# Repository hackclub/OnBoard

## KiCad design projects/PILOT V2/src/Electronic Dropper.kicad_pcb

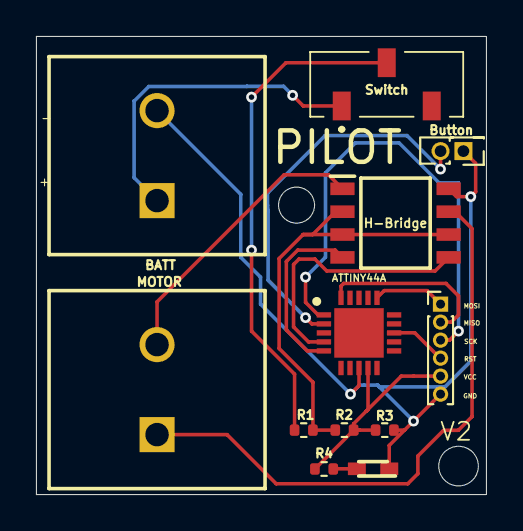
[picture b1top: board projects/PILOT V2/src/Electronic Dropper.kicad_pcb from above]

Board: 2 copper layers, 25.0 x 25.4 mm, 12 parts (0 on the bottom side), 15 nets.

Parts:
ATTINY44A: ATTINY44A-MU; ATTiny44a-MU
BATT: Battery; 1800408
H-Bridge: BD6221F-E2; SOIC127P620X171-8N
LED1: LED; Green led
MOTOR: 1800408
Programming-Pins1: Conn_01x06_Socket; PinHeader_1x06_P1.00mm_Vertical
R1: 270; R_0402_1005Metric
R2: 200; R_0402_1005Metric
R3: 1000; R_0402_1005Metric
R4: 300; R_0402_1005Metric
SW1: SW_Push; PinHeader_2x01_P1.27mm_Vertical
Switch: JS102011JCQN

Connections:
FIN: ATTINY44A.5 ((ADC0/AREF/PCINT0)_PA0), H-Bridge.4 (FIN)
GND: ATTINY44A.8 (GND), BATT.2 (-), H-Bridge.8 (GND), LED1.1 (K), Programming-Pins1.6, R3.2, SW1.1
unnamed: ATTINY44A.2 ((ADC3/T0/PCINT3)_PA3), SW1.2
unnamed: ATTINY44A.1 ((ADC4/USCK/SCL/T1/PCINT4)_PA4), Programming-Pins1.3
unnamed: ATTINY44A.20 (PA5_(ADC5/DO/MISO/OC1B/PCINT5)), Programming-Pins1.2
unnamed: ATTINY44A.16 (PA6_(PCINT6/OC1A/SDA/MOSI/DI/ADC6)), Programming-Pins1.1
unnamed: ATTINY44A.13 (PB3_(PCINT11/~RESET/DW)), Programming-Pins1.4
unnamed: BATT.1 (+), Switch.1
unnamed: H-Bridge.1 (OUT1), MOTOR.2
unnamed: H-Bridge.7 (OUT2), MOTOR.1
unnamed: LED1.2 (A), R4.2
unnamed: R1.2, Switch.2
RIN: ATTINY44A.4 ((ADC1/AIN0/PCINT1)_PA1), H-Bridge.5 (RIN)
VCC: ATTINY44A.9 (VCC), Programming-Pins1.5, R2.2, R3.1, R4.1
VCCQ: H-Bridge.2 (VCC_1), H-Bridge.3 (VCC_2), H-Bridge.6 (VREF), R1.1, R2.1

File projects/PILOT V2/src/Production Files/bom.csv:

Designator,Footprint,Quantity,Value,LCSC Part #
ATTINY44A,ATTiny44a-MU,1,ATTINY44A-MU,
BATT,1800408,1,Battery,
LED1,Green led,1,LED,
MOTOR,1800408,1,1800408,
R1,0402,1,270,
R2,0402,1,200,
R3,0402,1,1000,
R4,0402,1,300,
Switch,JS102011JCQN,1,JS102011JCQN,

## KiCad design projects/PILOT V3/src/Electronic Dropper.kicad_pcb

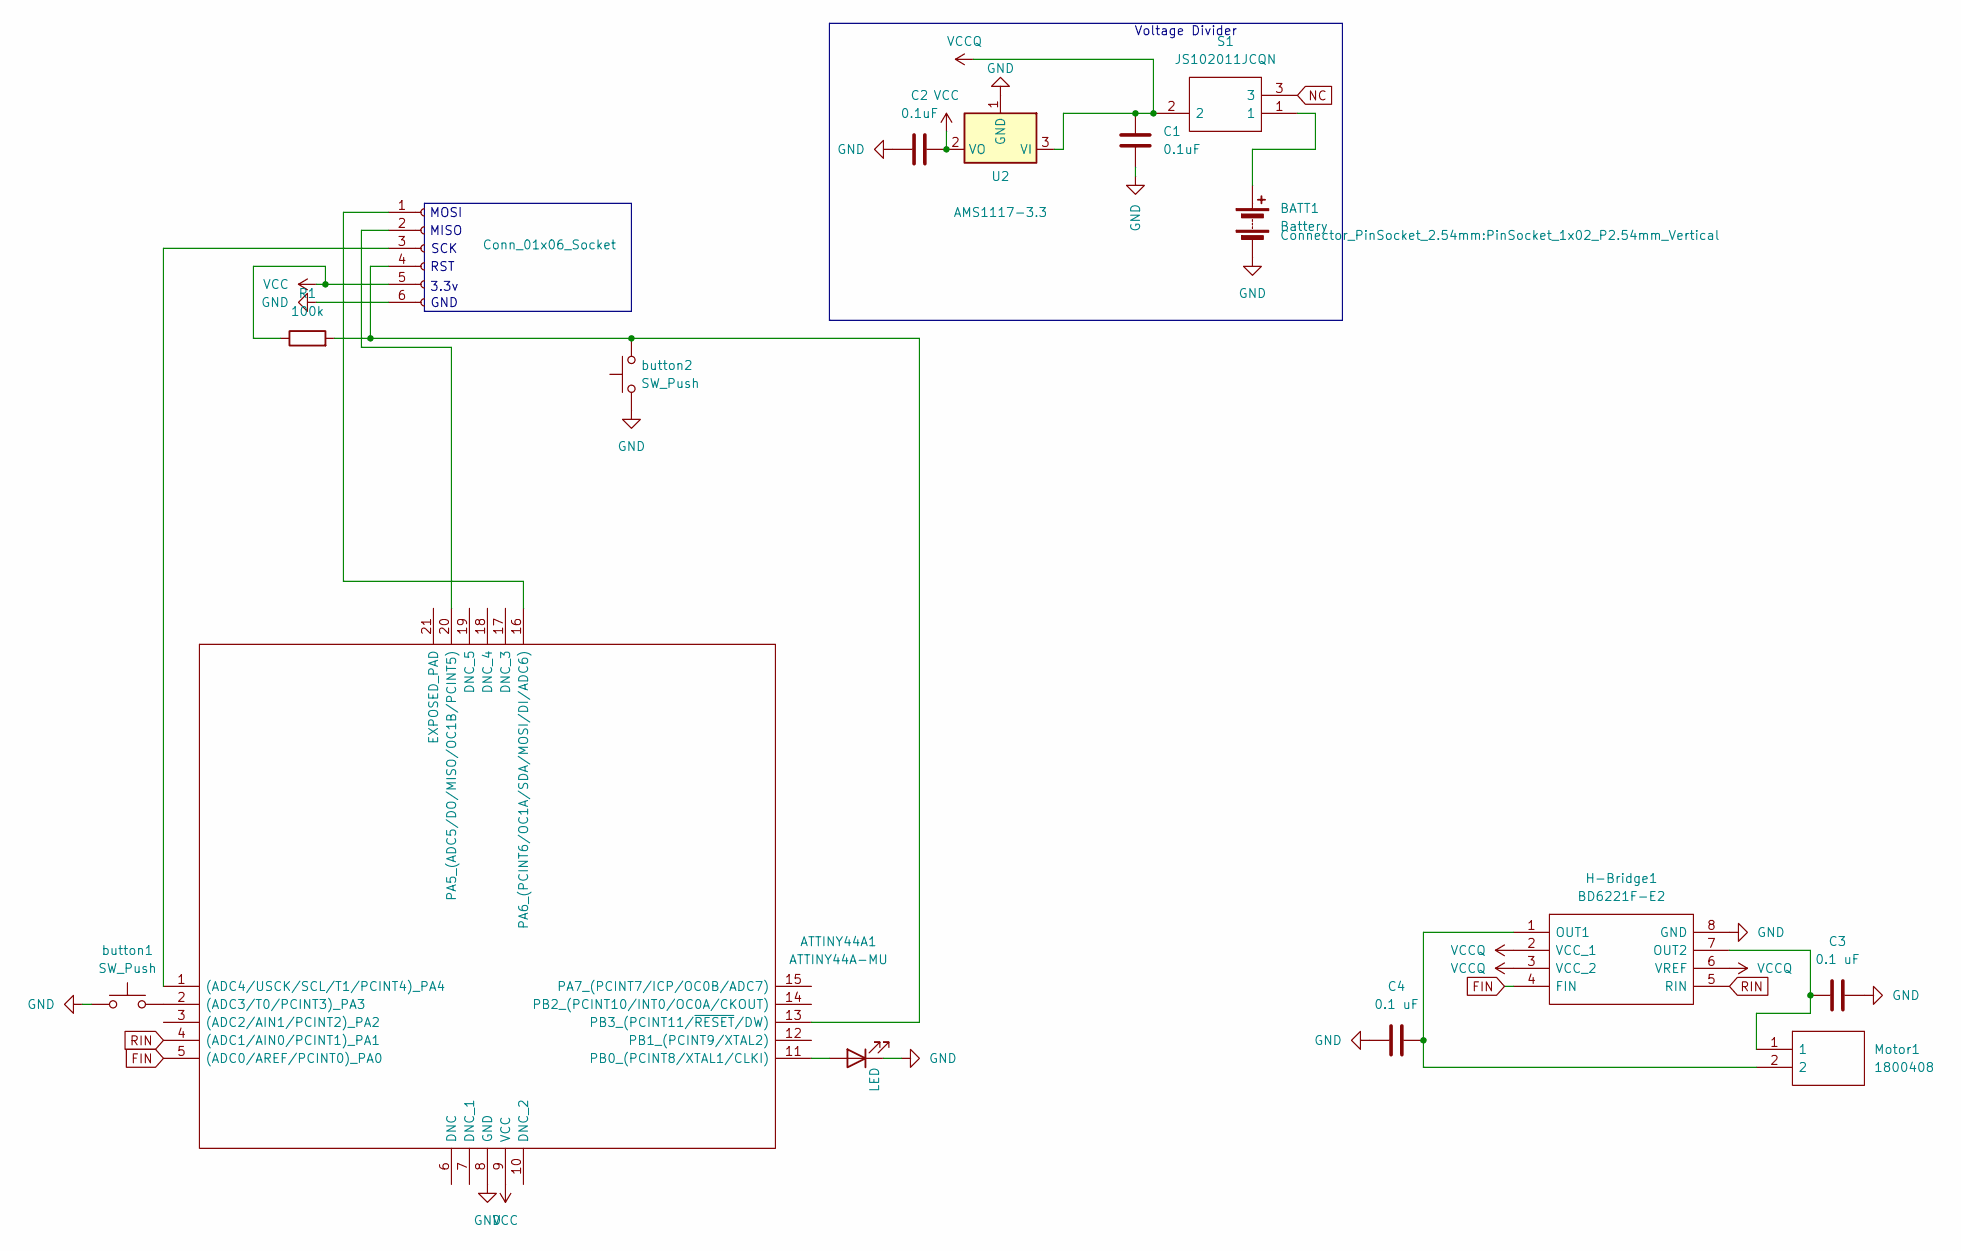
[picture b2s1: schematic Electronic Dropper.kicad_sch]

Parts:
ATTINY44A1: ATTINY44A-MU; ATTiny44a-MU; Manufacturer_Part_Number ATTINY44A-MU; Mouser Part Number 556-ATTINY44A-MU
BATT1: Battery; PinSocket_1x02_P2.54mm_Vertical
C1, C2: 0.1uF; C_0805_2012Metric
C3, C4: 0.1 uF; C_0805_2012Metric
H-Bridge1: BD6221F-E2; SOIC127P620X171-8N; Mouser Part Number 755-BD6221F-E2
LED1: LED; Green led
Motor1: 1800408; PinSocket_1x02_P2.54mm_Vertical
Programming-Pins1: Conn_01x06_Socket; PinHeader_1x06_P2.54mm_Vertical
R1: 100k; C_0402_1005Metric
S1: JS102011JCQN; Mouser Part Number 611-JS102011JCQN
U2: AMS1117-3.3; SOT-223-3_TabPin2
button1: SW_Push; PinSocket_1x02_P2.54mm_Vertical
button2: SW_Push; SW_PUSH_6mm

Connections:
FIN: ATTINY44A1.5 ((ADC0/AREF/PCINT0)_PA0), H-Bridge1.4 (FIN)
GND: ATTINY44A1.8 (GND), BATT1.2 (-), C1.2, C2.1, C3.2, C4.1, H-Bridge1.8 (GND), LED1.1 (K), Programming-Pins1.6, U2.1 (GND), button1.1, button2.1
NC: S1.3
unnamed: ATTINY44A1.2 ((ADC3/T0/PCINT3)_PA3), button1.2
unnamed: ATTINY44A1.1 ((ADC4/USCK/SCL/T1/PCINT4)_PA4), Programming-Pins1.3
unnamed: ATTINY44A1.20 (PA5_(ADC5/DO/MISO/OC1B/PCINT5)), Programming-Pins1.2
unnamed: ATTINY44A1.16 (PA6_(PCINT6/OC1A/SDA/MOSI/DI/ADC6)), Programming-Pins1.1
unnamed: ATTINY44A1.11 (PB0_(PCINT8/XTAL1/CLKI)), LED1.2 (A)
unnamed: ATTINY44A1.13 (PB3_(PCINT11/~RESET/DW)), Programming-Pins1.4, R1.2, button2.2
unnamed: BATT1.1 (+), S1.1
unnamed: C4.2, H-Bridge1.1 (OUT1), Motor1.2
unnamed: C3.1, H-Bridge1.7 (OUT2), Motor1.1
RIN: ATTINY44A1.4 ((ADC1/AIN0/PCINT1)_PA1), H-Bridge1.5 (RIN)
VCC: ATTINY44A1.9 (VCC), C2.2, Programming-Pins1.5, R1.1, U2.2 (VO)
VCCQ: C1.1, H-Bridge1.2 (VCC_1), H-Bridge1.3 (VCC_2), H-Bridge1.6 (VREF), S1.2, U2.3 (VI)

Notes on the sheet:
MOSI
RST
3.3v
Voltage Divider
GND
MISO
SCK

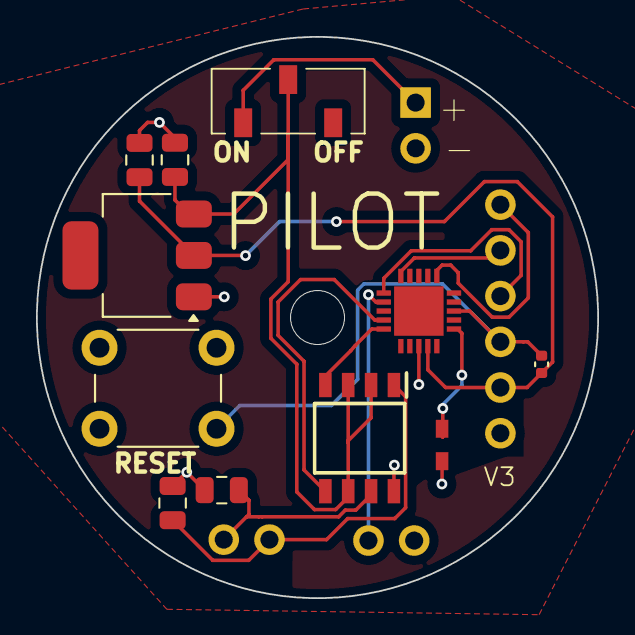
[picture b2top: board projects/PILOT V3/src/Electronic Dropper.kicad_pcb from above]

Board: 2 copper layers, 31.2 x 31.2 mm, 15 parts (0 on the bottom side), 14 nets.

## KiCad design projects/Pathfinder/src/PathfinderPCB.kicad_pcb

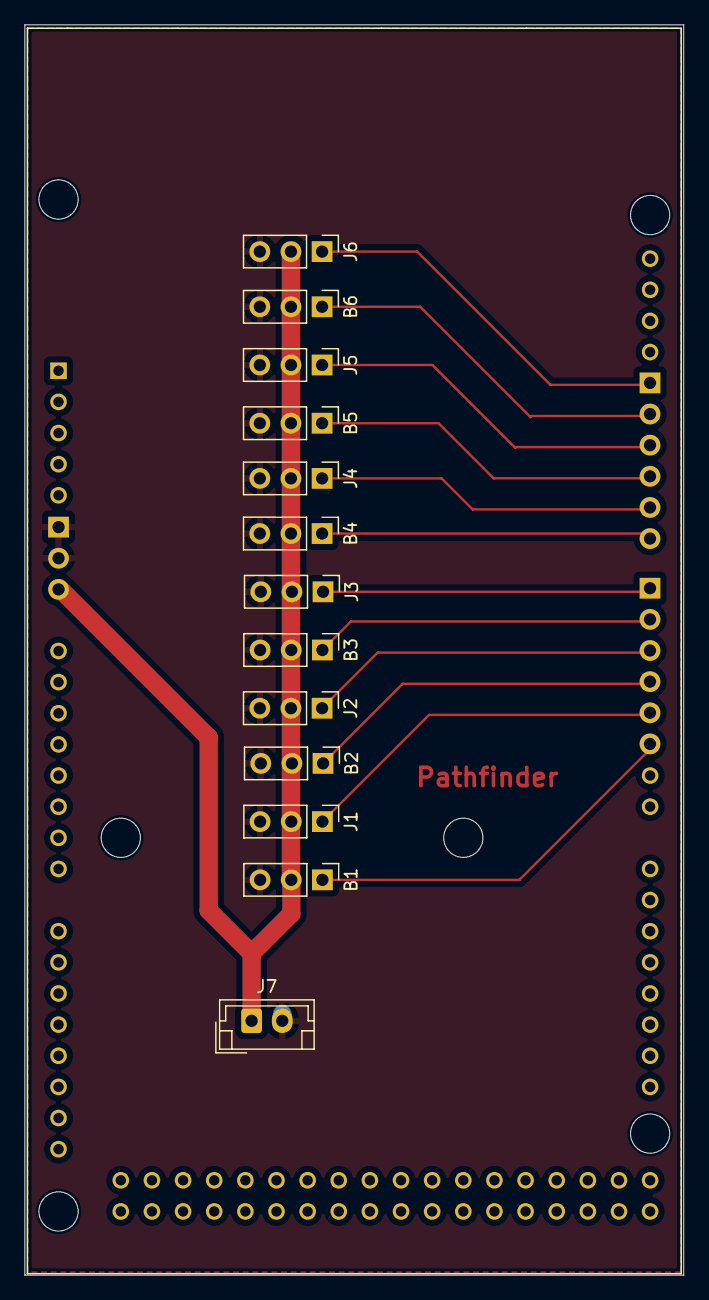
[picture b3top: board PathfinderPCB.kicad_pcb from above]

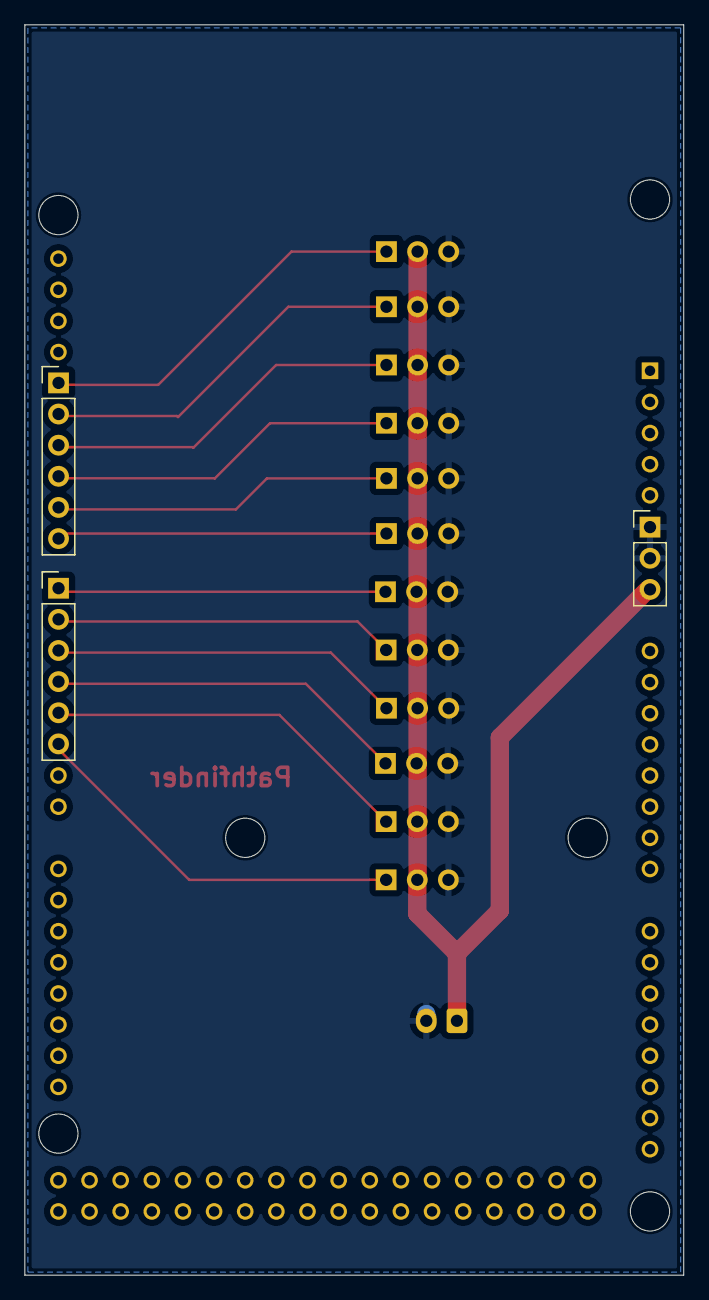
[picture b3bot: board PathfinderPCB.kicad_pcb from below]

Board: 2 copper layers, 53.8 x 102.0 mm, 17 parts (3 on the bottom side), 14 nets.

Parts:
A1: ARDUINO_MEGA_2560_REV3_A000067; ARDUINO_ARDUINO_MEGA_2560_REV3_A000067
B1, B2, B3, B4, B5, B6: Motor_Servo; PinHeader_1x03_P2.54mm_Vertical
J1, J2, J3, J4, J5, J6: Motor_Servo; PinHeader_1x03_P2.54mm_Vertical
J7: Conn_01x02_Pin; JST_EH_B2B-EH-A_1x02_P2.50mm_Vertical
J8, J9: Conn_01x06_Pin; PinHeader_1x06_P2.54mm_Vertical
J10: Conn_01x03_Pin; PinHeader_1x03_P2.54mm_Vertical

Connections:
+5V: B1.2 (5V), B2.2 (5V), B3.2 (5V), B4.2 (5V), B5.2 (5V), B6.2 (5V), J1.2 (5V), J2.2 (5V), J3.2 (5V), J4.2 (5V), J5.2 (5V), J6.2 (5V), J7.1, J10.3
GND: B1.3 (GND), B2.3 (GND), B3.3 (GND), B4.3 (GND), B5.3 (GND), B6.3 (GND), J1.3 (GND), J2.3 (GND), J3.3 (GND), J4.3 (GND), J5.3 (GND), J6.3 (GND), J7.2, J10.1, J10.2
unnamed: B1.1 (PWM), J8.6
unnamed: B2.1 (PWM), J8.4
unnamed: B3.1 (PWM), J8.2
unnamed: B4.1 (PWM), J9.6
unnamed: B5.1 (PWM), J9.4
unnamed: B6.1 (PWM), J9.2
unnamed: J1.1 (PWM), J8.5
unnamed: J2.1 (PWM), J8.3
unnamed: J3.1 (PWM), J8.1
unnamed: J4.1 (PWM), J9.5
unnamed: J5.1 (PWM), J9.3
unnamed: J6.1 (PWM), J9.1

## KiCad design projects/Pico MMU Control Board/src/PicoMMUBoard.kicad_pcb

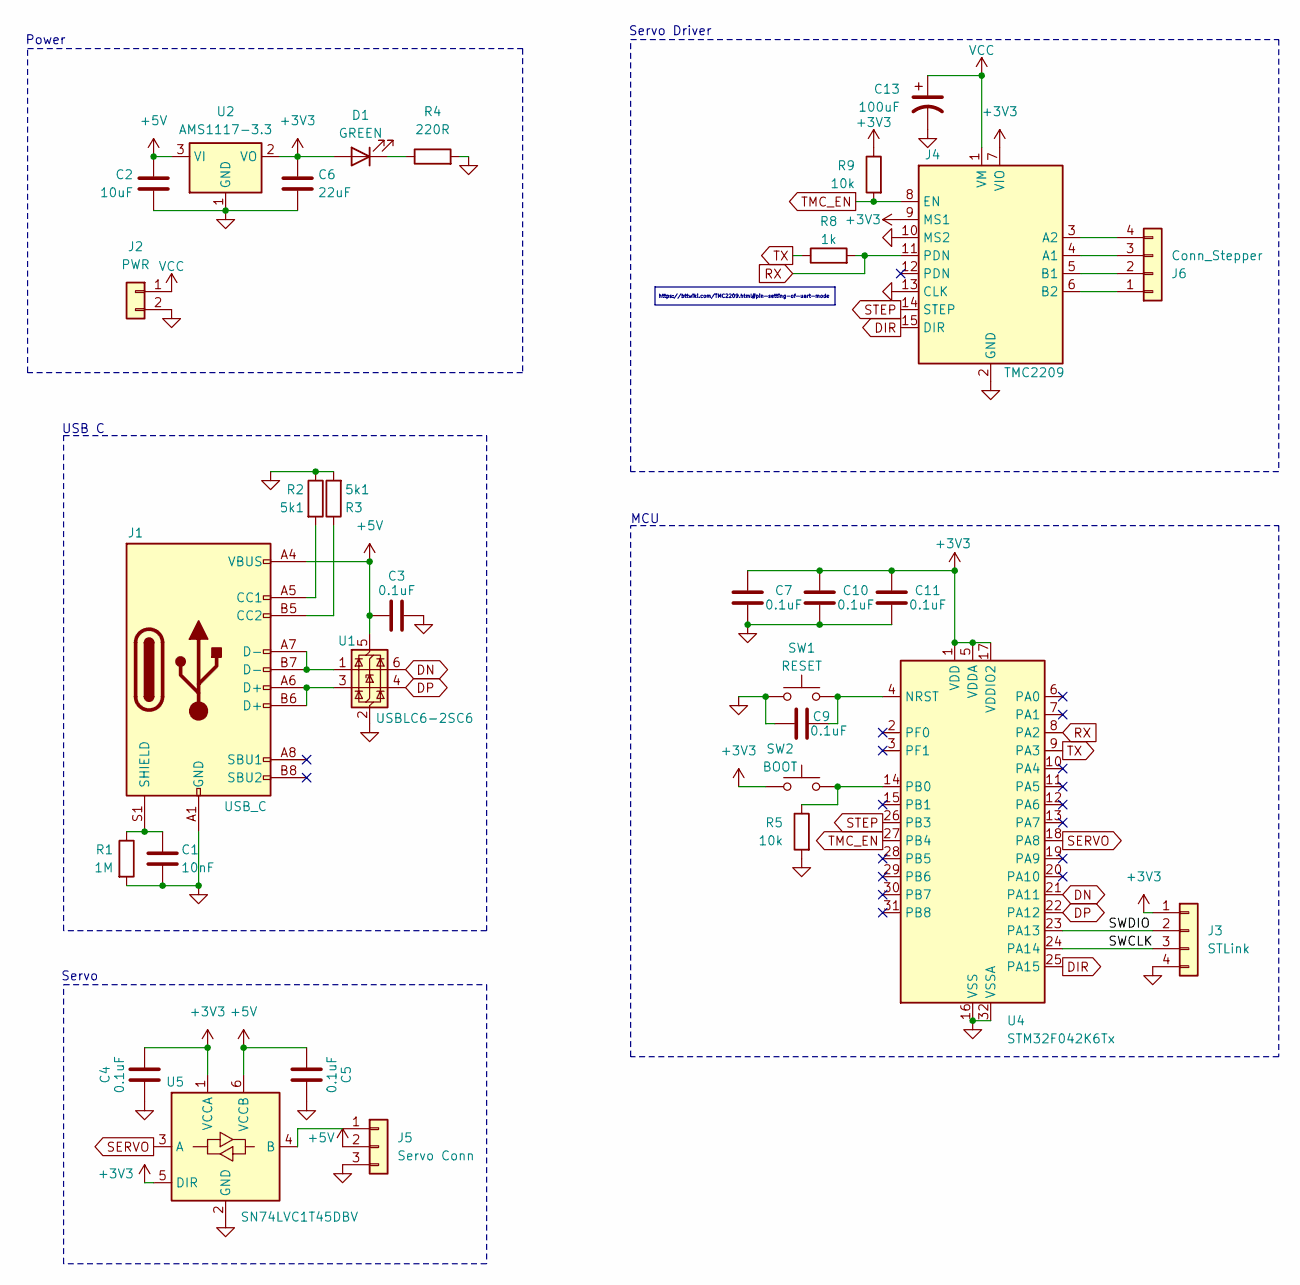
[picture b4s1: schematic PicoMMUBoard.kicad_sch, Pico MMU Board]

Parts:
C1: 10nF; C_0603_1608Metric
C2: 10uF; C_0603_1608Metric
C3, C4, C5, C7, C9, C10, C11: 0.1uF; C_0603_1608Metric
C6: 22uF; C_0603_1608Metric
C13: 100uF; C_Elec_6.3x7.7; LCSC C3151829
D1: GREEN; LED_0805_2012Metric; LCSC C2297
J1: USB_C; USB_C_Receptacle_GCT_USB4105-xx-A_16P_TopMnt_Horizontal; LCSC C165948
J2: PWR; TerminalBlock_MetzConnect_Type073_RT02602HBLU_1x02_P5.08mm_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; LCSC C8465
J3: STLink; PinHeader_1x04_P2.54mm_Vertical
J4: TMC2209
J5: Servo Conn; PinHeader_1x03_P2.54mm_Vertical; LCSC C144394
J6: Conn_Stepper; JST_XH_B4B-XH-A_1x04_P2.50mm_Vertical; LCSC C594232
R1: 1M; R_0603_1608Metric
R2, R3: 5k1; R_0603_1608Metric
R4: 220R; R_0603_1608Metric
R5, R9: 10k; R_0603_1608Metric
R8: 1k; R_0603_1608Metric
SW1: RESET; SW4_KMS-P; LCSC C221703
SW2: BOOT; SW4_KMS-P; LCSC C221703
U1: USBLC6-2SC6; SOT-23-6; LCSC C2827654
U2: AMS1117-3.3; SOT-223-3_TabPin2; LCSC C6186
U4: STM32F042K6Tx; LQFP-32_7x7mm_P0.8mm; LCSC C1337340
U5: SN74LVC1T45DBV; SOT-23-6; LCSC C7843

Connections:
+3V3: C4.2, C6.1, C7.2, C10.2, C11.2, D1.2 (A), J3.1, J4.7 (VIO), J4.9 (MS1), R9.1, SW2.1, U2.2 (VO), U4.1 (VDD), U4.5 (VDDA), U4.17 (VDDIO2), U5.1 (VCCA), U5.5 (DIR)
+5V: C2.1, C3.1, C5.1, J1.A4 (VBUS), J1.A9 (VBUS), J1.B4 (VBUS), J1.B9 (VBUS), J5.2, U1.5 (VBUS), U2.3 (VI), U5.6 (VCCB)
/SWCLK: J3.3, U4.24 (PA14)
/SWDIO: J3.2, U4.23 (PA13)
DIR: J4.15 (DIR), U4.25 (PA15)
DN: U1.6 (I/O1), U4.21 (PA11)
DP: U1.4 (I/O2), U4.22 (PA12)
GND: C1.2, C2.2, C3.2, C4.1, C5.2, C6.2, C7.1, C9.2, C10.1, C11.1, C13.2, J1.A1 (GND), J1.A12 (GND), J1.B1 (GND), J1.B12 (GND), J2.2, J3.4, J4.2 (GND), J4.10 (MS2), J4.13 (CLK), J5.3, R1.2, R2.1, R3.2, R4.2, R5.2, SW1.1, U1.2 (GND), U2.1 (GND), U4.16 (VSS), U4.32 (VSSA), U5.2 (GND)
unnamed: D1.1 (K), R4.1
unnamed: J1.A5 (CC1), R2.2
unnamed: J1.B5 (CC2), R3.1
unnamed: J1.A6 (D+), J1.B6 (D+), U1.3 (I/O2)
unnamed: J1.A7 (D-), J1.B7 (D-), U1.1 (I/O1)
unnamed: C1.1, J1.S1 (SHIELD), R1.1
unnamed: J4.4 (A1), J6.3
unnamed: J4.3 (A2), J6.4
unnamed: J4.5 (B1), J6.2
unnamed: J4.6 (B2), J6.1
unnamed: J5.1, U5.4 (B)
unnamed: C9.1, SW1.2, U4.4 (NRST)
unnamed: R5.1, SW2.2, U4.14 (PB0)
RX: J4.11 (PDN), R8.2, U4.8 (PA2)
SERVO: U4.18 (PA8), U5.3 (A)
STEP: J4.14 (STEP), U4.26 (PB3)
TMC_EN: J4.8 (EN), R9.2, U4.27 (PB4)
TX: R8.1, U4.9 (PA3)
VCC: C13.1, J2.1, J4.1 (VM)

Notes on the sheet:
https://bttwiki.com/TMC2209.html#pin-setting-of-uart-mode
Power
Servo
MCU
USB C
Servo Driver

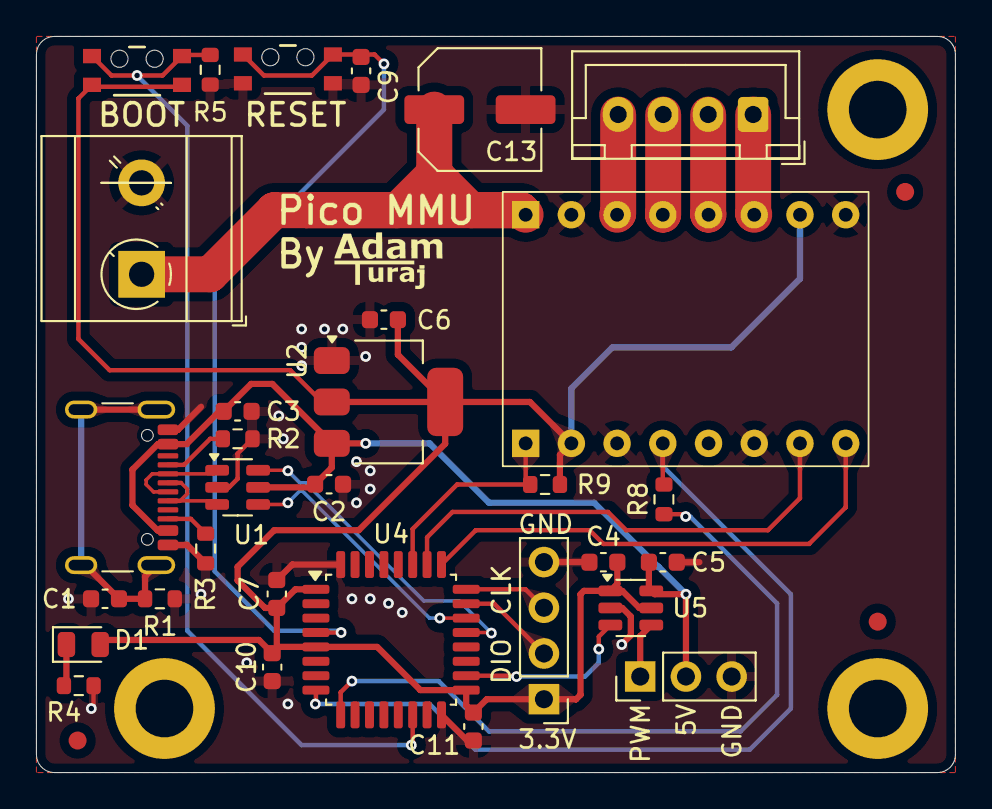
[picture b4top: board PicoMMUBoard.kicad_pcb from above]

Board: 2 copper layers, 51.1 x 40.9 mm, 31 parts (0 on the bottom side), 27 nets.

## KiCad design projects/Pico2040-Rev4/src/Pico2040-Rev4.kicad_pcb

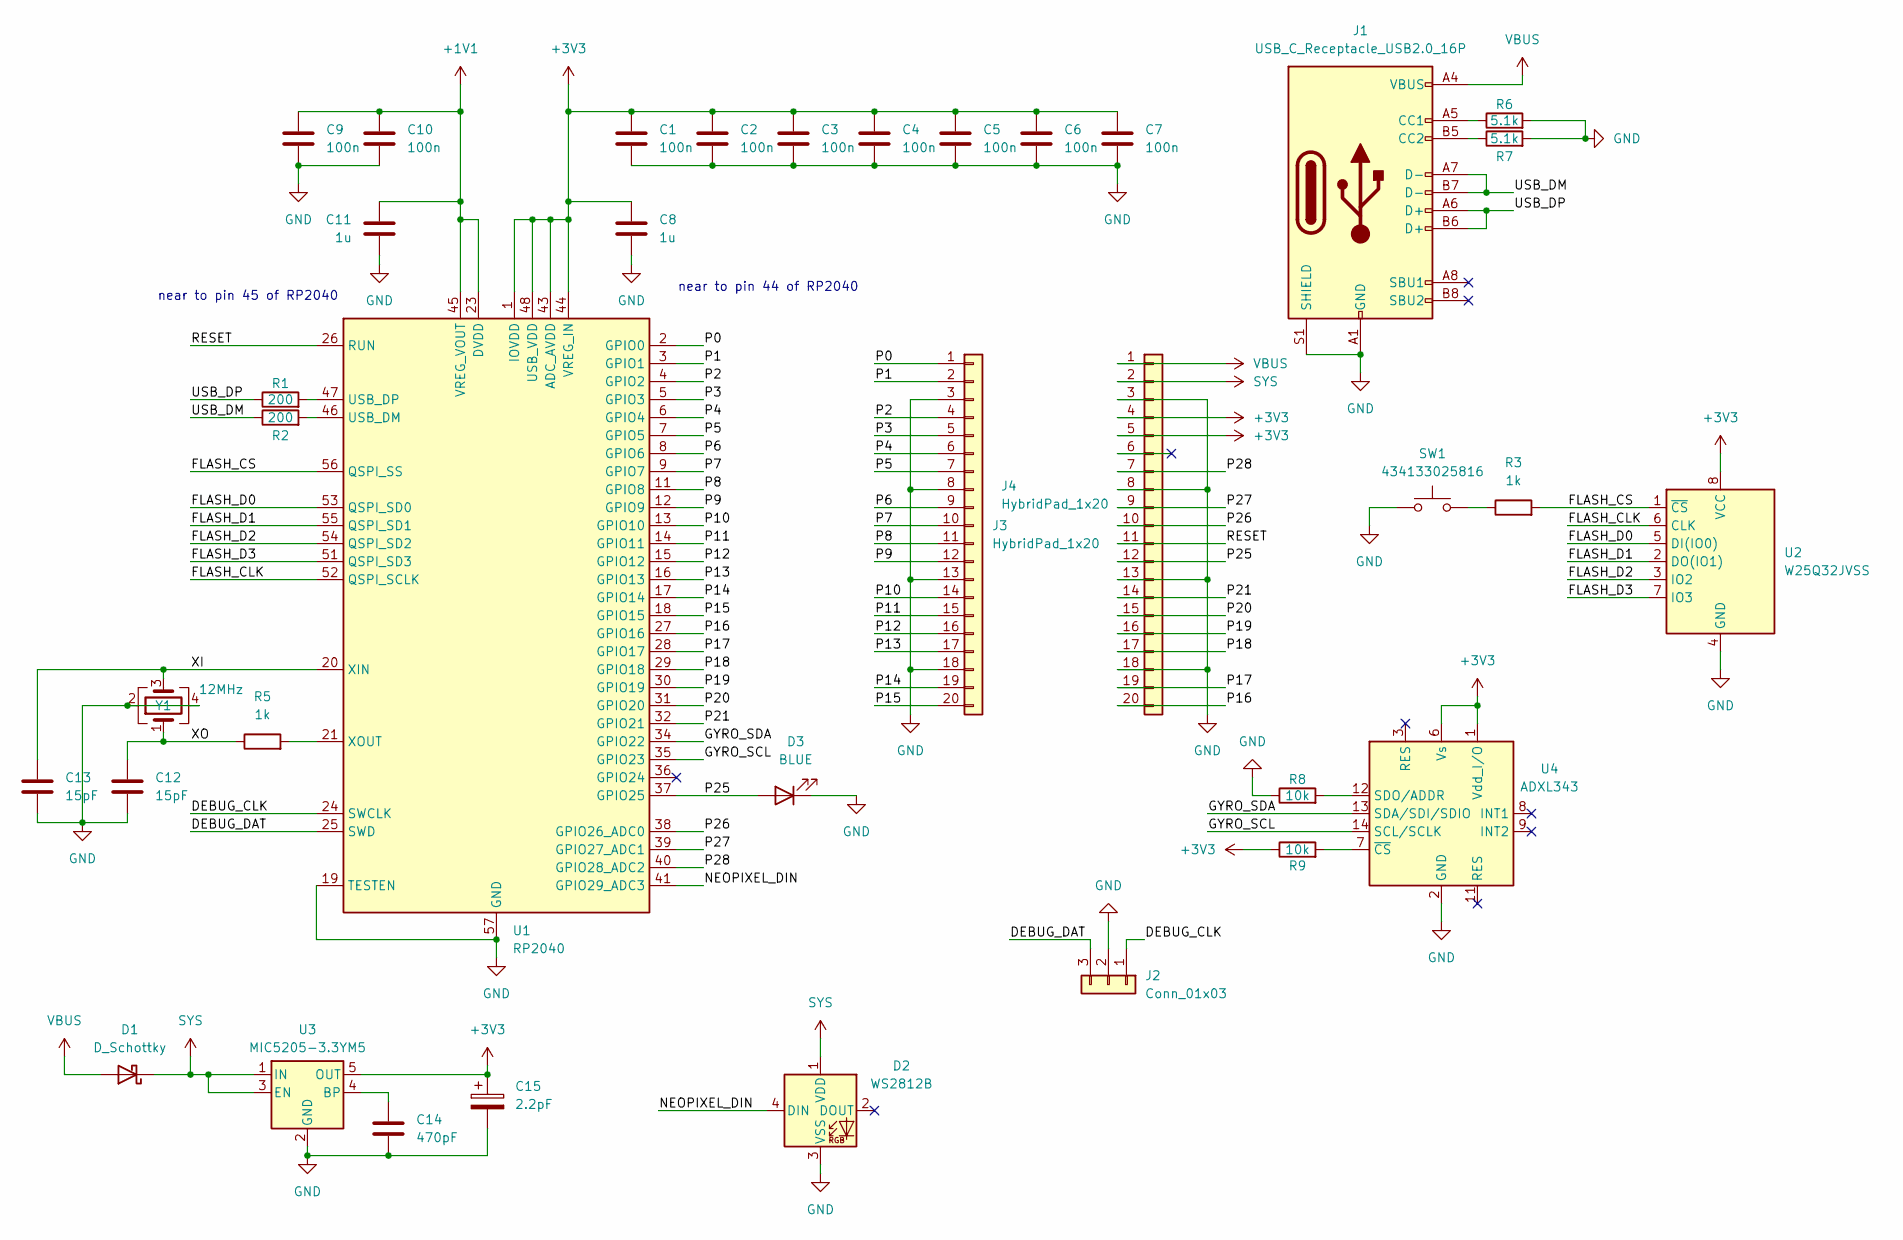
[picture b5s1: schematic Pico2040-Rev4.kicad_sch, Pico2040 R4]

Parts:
C1, C2, C3, C4, C5, C6, C7, C9, C10: 100n; C_0402_1005Metric
C8, C11: 1u; C_0402_1005Metric
C12, C13: 15pF; C_0402_1005Metric
C14: 470pF; C_0402_1005Metric
C15: 2.2pF; CP_EIA-1608-08_AVX-J
D1: D_Schottky; D_SOD-123F
D2: WS2812B; LED_WS2812B_PLCC4_5.0x5.0mm_P3.2mm
D3: BLUE; LED_0402_1005Metric
J1: USB_C_Receptacle_USB2.0_16P; USB_C_Receptacle_GCT_USB4105-xx-A_16P_TopMnt_Horizontal
J2: Conn_01x03; PinHeader_1x03_P2.54mm_Vertical
J3, J4: HybridPad_1x20; Conn_01x20_2.54mm
R1, R2: 200; R_0402_1005Metric
R3, R5: 1k; R_0402_1005Metric
R6, R7: 5.1k; R_0402_1005Metric
R8, R9: 10k; R_0402_1005Metric
SW1: 434133025816; SW_Push_1P1T_NO_Vertical_Wuerth_434133025816
U1: RP2040; QFN-56-1EP_7x7mm_P0.4mm_EP3.2x3.2mm
U2: W25Q32JVSS; 8-USON-2X3
U3: MIC5205-3.3YM5; SOT-23-5
U4: ADXL343; LGA-14_3x5mm_P0.8mm_LayoutBorder1x6y
Y1: 12MHz; Crystal_SMD_2520-4Pin_2.5x2.0mm

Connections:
+1V1: C9.1, C10.1, C11.1, U1.23 (DVDD), U1.45 (VREG_VOUT), U1.50 (DVDD)
+3V3: C1.1, C2.1, C3.1, C4.1, C5.1, C6.1, C7.1, C8.1, C15.1, J4.4, J4.5, R9.1, U1.1 (IOVDD), U1.10 (IOVDD), U1.22 (IOVDD), U1.33 (IOVDD), U1.42 (IOVDD), U1.43 (ADC_AVDD), U1.44 (VREG_IN), U1.48 (USB_VDD), U1.49 (IOVDD), U2.8 (VCC), U3.5 (OUT), U4.1 (Vdd_I/O), U4.6 (Vs)
/DEBUG_CLK: J2.1, U1.24 (SWCLK)
/DEBUG_DAT: J2.3, U1.25 (SWD)
/FLASH_CLK: U1.52 (QSPI_SCLK), U2.6 (CLK)
/FLASH_CS: R3.2, U1.56 (QSPI_SS), U2.1 (~CS)
/FLASH_D0: U1.53 (QSPI_SD0), U2.5 (DI(IO0))
/FLASH_D1: U1.55 (QSPI_SD1), U2.2 (DO(IO1))
/FLASH_D2: U1.54 (QSPI_SD2), U2.3 (IO2)
/FLASH_D3: U1.51 (QSPI_SD3), U2.7 (IO3)
/GYRO_SCL: U1.35 (GPIO23), U4.14 (SCL/SCLK)
/GYRO_SDA: U1.34 (GPIO22), U4.13 (SDA/SDI/SDIO)
/NEOPIXEL_DIN: D2.4 (DIN), U1.41 (GPIO29_ADC3)
/P0: J3.1, U1.2 (GPIO0)
/P1: J3.2, U1.3 (GPIO1)
/P2: J3.4, U1.4 (GPIO2)
/P3: J3.5, U1.5 (GPIO3)
/P4: J3.6, U1.6 (GPIO4)
/P5: J3.7, U1.7 (GPIO5)
/P6: J3.9, U1.8 (GPIO6)
/P7: J3.10, U1.9 (GPIO7)
/P8: J3.11, U1.11 (GPIO8)
/P9: J3.12, U1.12 (GPIO9)
/P10: J3.14, U1.13 (GPIO10)
/P11: J3.15, U1.14 (GPIO11)
/P12: J3.16, U1.15 (GPIO12)
/P13: J3.17, U1.16 (GPIO13)
/P14: J3.19, U1.17 (GPIO14)
/P15: J3.20, U1.18 (GPIO15)
/P16: J4.20, U1.27 (GPIO16)
/P17: J4.19, U1.28 (GPIO17)
/P18: J4.17, U1.29 (GPIO18)
/P19: J4.16, U1.30 (GPIO19)
/P20: J4.15, U1.31 (GPIO20)
/P21: J4.14, U1.32 (GPIO21)
/P25: D3.2 (A), J4.12, U1.37 (GPIO25)
/P26: J4.10, U1.38 (GPIO26_ADC0)
/P27: J4.9, U1.39 (GPIO27_ADC1)
/P28: J4.7, U1.40 (GPIO28_ADC2)
/RESET: J4.11, U1.26 (RUN)
/USB_DM: J1.A7 (D-), J1.B7 (D-), R2.1
/USB_DP: J1.A6 (D+), J1.B6 (D+), R1.1
/XI: C13.1, U1.20 (XIN), Y1.3
/XO: C12.1, R5.1, Y1.1
GND: C1.2, C2.2, C3.2, C4.2, C5.2, C6.2, C7.2, C8.2, C9.2, C10.2, C11.2, C12.2, C13.2, C14.2, C15.2, D2.3 (VSS), D3.1 (K), J1.A1 (GND), J1.A12 (GND), J1.B1 (GND), J1.B12 (GND), J1.S1 (SHIELD), J2.2, J3.3, J3.8, J3.13, J3.18, J4.3, J4.8, J4.13, J4.18, R6.2, R7.2, R8.1, SW1.1, U1.19 (TESTEN), U1.57 (GND), U2.4 (GND), U3.2 (GND), U4.2 (GND), U4.4 (GND), U4.5 (GND), Y1.2, Y1.4
unnamed: J1.A5 (CC1), R6.1
unnamed: J1.B5 (CC2), R7.1
unnamed: R3.1, SW1.2
unnamed: R2.2, U1.46 (USB_DM)
unnamed: R1.2, U1.47 (USB_DP)
unnamed: R5.2, U1.21 (XOUT)
unnamed: C14.1, U3.4 (BP)
unnamed: R8.2, U4.12 (SDO/ADDR)
unnamed: R9.2, U4.7 (~CS)
SYS: D1.1 (K), D2.1 (VDD), J4.2, U3.1 (IN), U3.3 (EN)
VBUS: D1.2 (A), J1.A4 (VBUS), J1.A9 (VBUS), J1.B4 (VBUS), J1.B9 (VBUS), J4.1

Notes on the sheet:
near to pin 44 of RP2040
near to pin 45 of RP2040

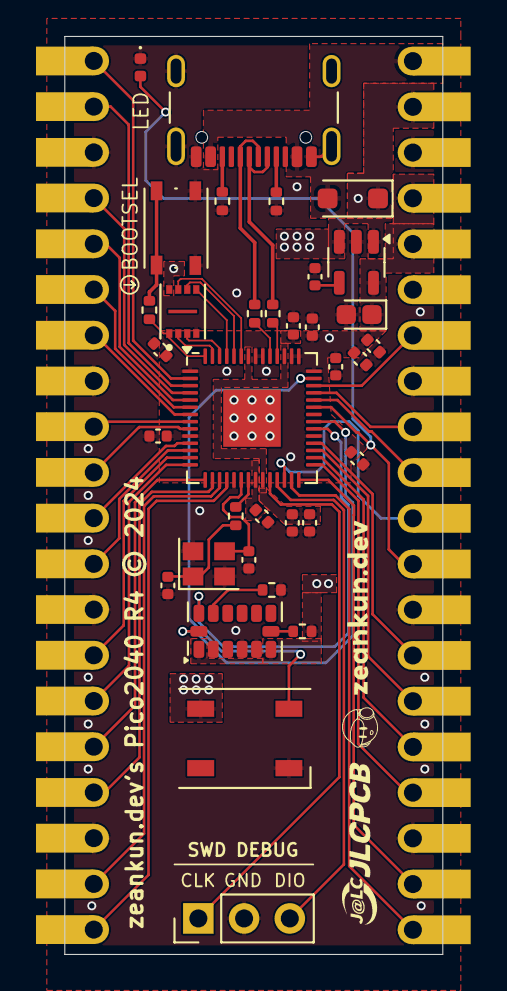
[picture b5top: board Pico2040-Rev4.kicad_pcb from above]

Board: 2 copper layers, 21.0 x 51.0 mm, 36 parts (1 on the bottom side), 56 nets.

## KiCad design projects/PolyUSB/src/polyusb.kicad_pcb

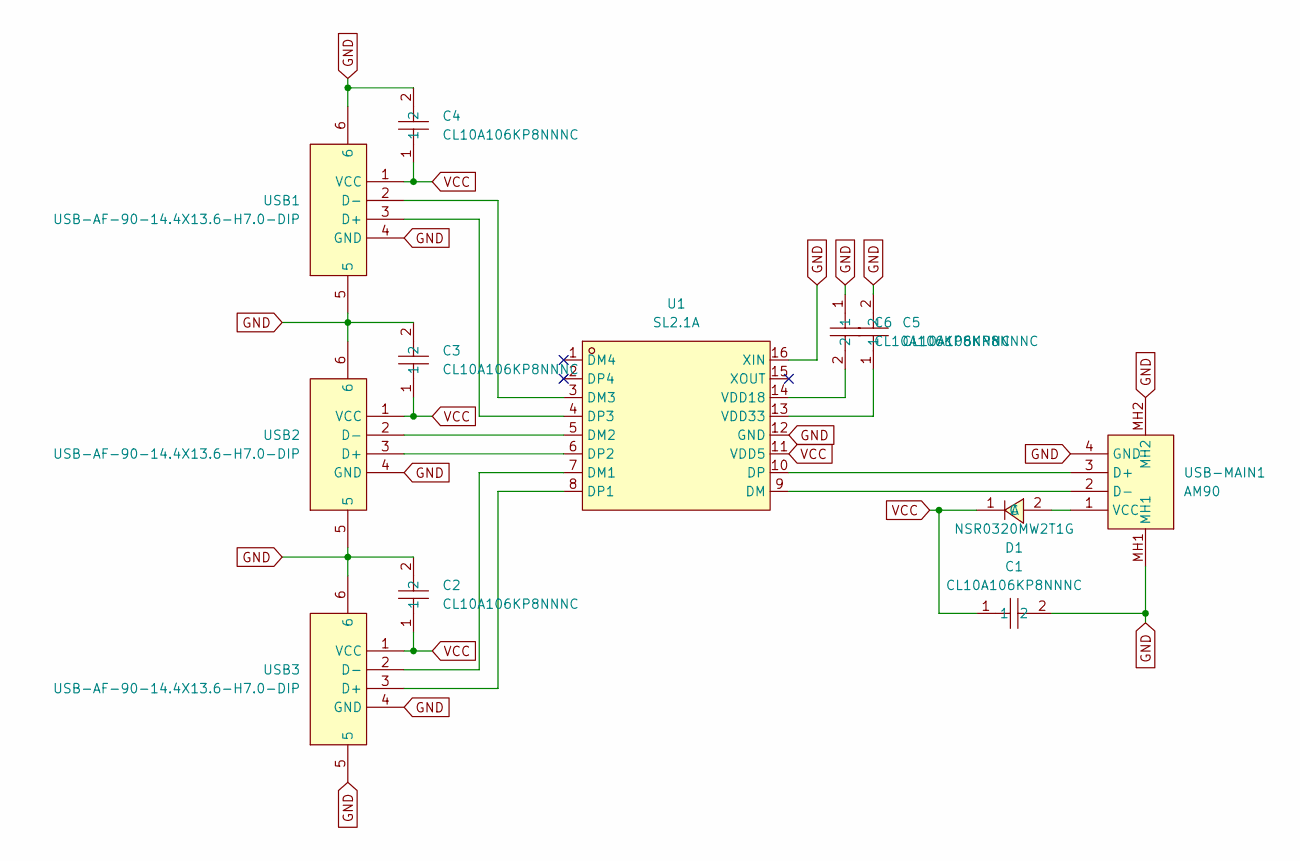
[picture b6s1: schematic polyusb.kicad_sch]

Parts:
C1, C2, C3, C4, C5, C6: CL10A106KP8NNNC; C0603; LCSC Part C19702
D1: NSR0320MW2T1G; SOD-323_L1.8-W1.3-LS2.5-RD; LCSC Part C48192
U1: SL2.1A; SOP-16_L10.0-W3.9-P1.27-LS6.0-BL; LCSC Part C192893
USB1, USB2, USB3: USB-AF-90-14.4X13.6-H7.0-DIP; USB-A-TH_C46407; LCSC Part C46407
USB-MAIN1: AM90; USB-AM-TH_AM90; LCSC Part C404965

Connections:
GND: C1.2, C2.2, C3.2, C4.2, C5.2, C6.1, U1.12 (GND), U1.16 (XIN), USB1.4 (GND), USB1.5, USB1.6, USB2.4 (GND), USB2.5, USB2.6, USB3.4 (GND), USB3.5, USB3.6, USB-MAIN1.4 (GND), USB-MAIN1.MH1, USB-MAIN1.MH2
unnamed: D1.2 (A), USB-MAIN1.1 (VCC)
unnamed: U1.7 (DM1), USB3.2 (D-)
unnamed: U1.5 (DM2), USB2.2 (D-)
unnamed: U1.3 (DM3), USB1.2 (D-)
unnamed: U1.9 (DM), USB-MAIN1.2 (D-)
unnamed: U1.8 (DP1), USB3.3 (D+)
unnamed: U1.6 (DP2), USB2.3 (D+)
unnamed: U1.4 (DP3), USB1.3 (D+)
unnamed: U1.10 (DP), USB-MAIN1.3 (D+)
unnamed: C6.2, U1.14 (VDD18)
unnamed: C5.1, U1.13 (VDD33)
VCC: C1.1, C2.1, C3.1, C4.1, D1.1 (C), U1.11 (VDD5), USB1.1 (VCC), USB2.1 (VCC), USB3.1 (VCC)

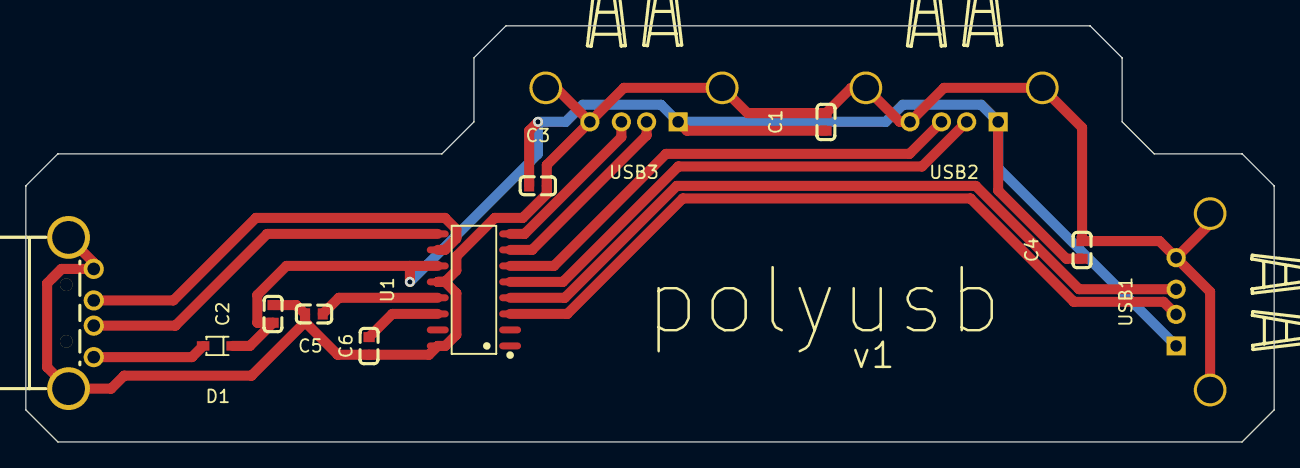
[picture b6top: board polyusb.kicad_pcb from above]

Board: 2 copper layers, 99.1 x 33.0 mm, 12 parts (0 on the bottom side), 13 nets.

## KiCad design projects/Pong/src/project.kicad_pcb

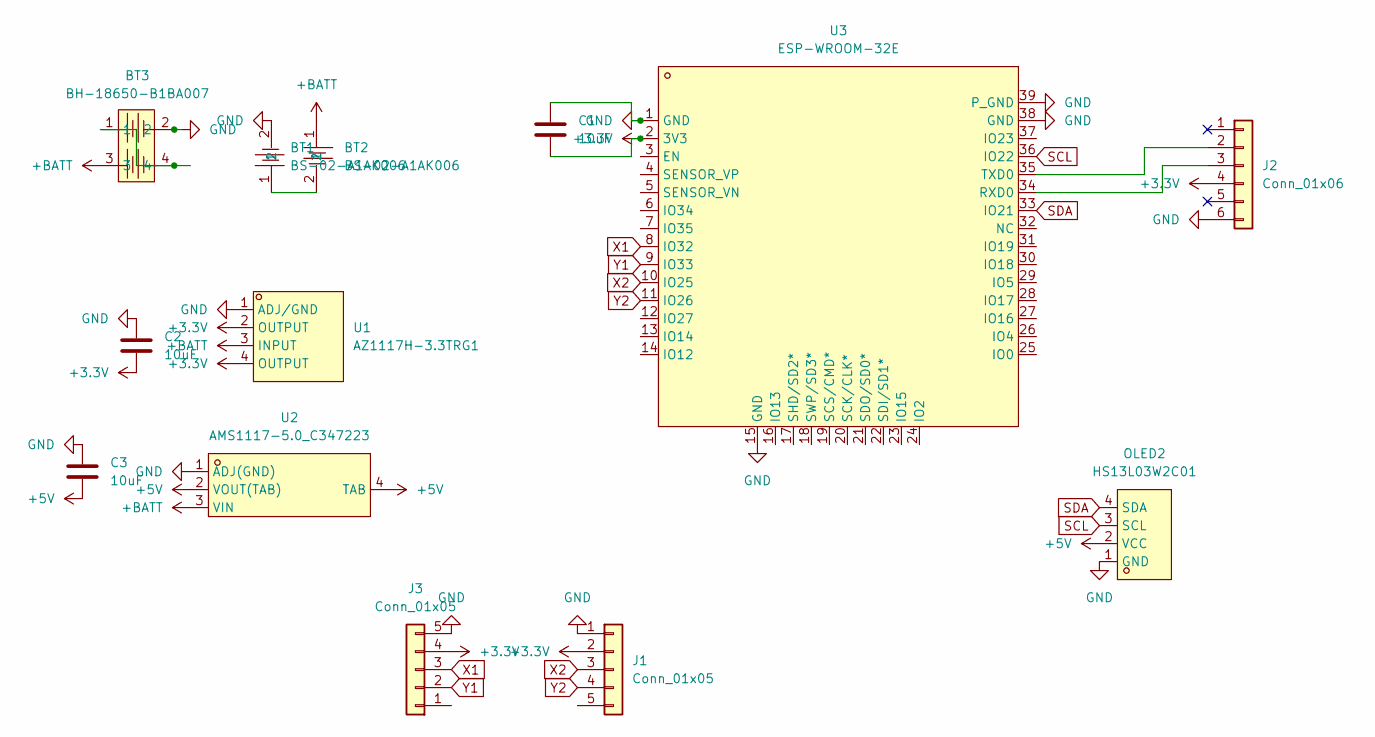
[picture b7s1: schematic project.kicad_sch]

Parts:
BT1, BT2: BS-02-A1AK006; BAT-TH_BS-02-A1AK006; LCSC Part C964746
BT3: BH-18650-B1BA007; BAT-SMD_BH-18650-B1BA007; LCSC Part C6937126
C1, C2, C3: 10uF; C_0603_1608Metric; LCSC C19702
J1, J3: Conn_01x05; PinSocket_1x05_P2.54mm_Horizontal
J2: Conn_01x06; PinSocket_1x06_P2.54mm_Vertical
OLED2: HS13L03W2C01; OLED-TH_L35.4-W33.5_HS13L03W2C01; LCSC Part C7465997
U1: AZ1117H-3.3TRG1; SOT-223-3_L6.5-W3.4-P2.30-LS7.0-BR; LCSC Part C110474
U2: AMS1117-5.0_C347223; SOT-223_L6.7-W3.5-P2.30-BR; LCSC Part C347223
U3: ESP-WROOM-32E; COMM-SMD_ESP-WROOM-32D; LCSC Part C19949066

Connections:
+3.3V: C1.1, C2.1, J1.2, J2.4, J3.4, U1.2 (OUTPUT), U1.4 (OUTPUT), U3.2 (3V3)
+5V: C3.1, OLED2.2 (VCC), U2.2 (VOUT(TAB)), U2.4 (TAB)
+BATT: BT2.1, BT3.3, U1.3 (INPUT), U2.3 (VIN)
GND: BT1.2, BT3.2, C1.2, C2.2, C3.2, J1.1, J2.6, J3.5, OLED2.1 (GND), U1.1 (ADJ/GND), U2.1 (ADJ(GND)), U3.1 (GND), U3.15 (GND), U3.38 (GND), U3.39 (P_GND)
unnamed: BT1.1, BT2.2
unnamed: BT3.1, BT3.4
unnamed: J2.2, U3.35 (TXD0)
unnamed: J2.3, U3.34 (RXD0)
SCL: OLED2.3 (SCL), U3.36 (IO22)
SDA: OLED2.4 (SDA), U3.33 (IO21)
X1: J3.3, U3.8 (IO32)
X2: J1.3, U3.10 (IO25)
Y1: J3.2, U3.9 (IO33)
Y2: J1.4, U3.11 (IO26)

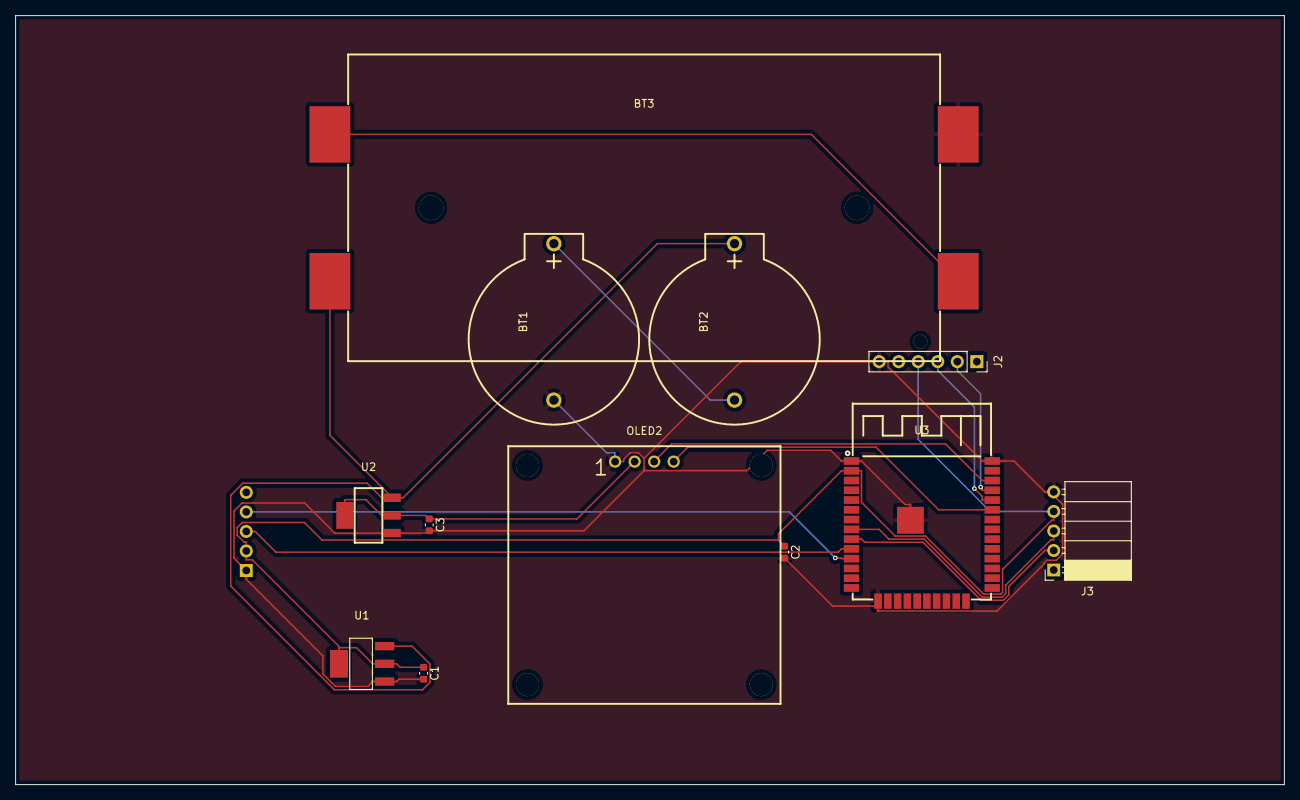
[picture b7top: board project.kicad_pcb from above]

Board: 2 copper layers, 165.0 x 100.0 mm, 13 parts (1 on the bottom side), 14 nets.

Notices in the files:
projects/Pico2040-Rev4/src/Pico2040-Rev4.kicad_pcb:
licensed by Book's
©️ 2024 zeankun.dev.
logo ©️ choco panda kat
all rights reserved
zeankun.dev's Pico2040 R4 ©️ 2024
